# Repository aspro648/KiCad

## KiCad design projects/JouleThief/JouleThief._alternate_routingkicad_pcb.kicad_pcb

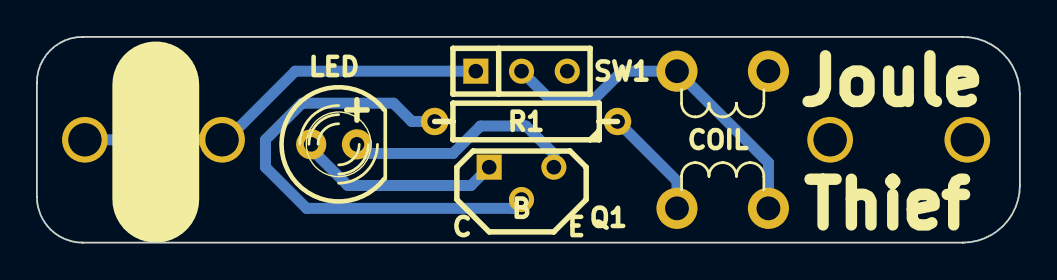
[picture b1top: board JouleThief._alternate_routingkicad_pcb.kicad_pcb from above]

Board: 2 copper layers, 54.6 x 11.4 mm, 6 parts (0 on the bottom side), 6 nets.

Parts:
BT1: BATTERY; BAT_CLIP
LED: LED; LED-5MM
Q1: PN2222A; TO92-123
R1: 1000; R4
SW1: SPST; MICROSWITCH_SPST
T1: COIL; TRANS_JOULE_THIEF

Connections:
/GND: BT1.2, LED.2, Q1.1
unnamed: LED.1, Q1.3, T1.3
unnamed: Q1.2, R1.2
unnamed: R1.1, T1.2
unnamed: SW1.2, T1.1, T1.4
unnamed: BT1.1, SW1.1

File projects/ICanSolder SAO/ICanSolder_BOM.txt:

1 ea., SW1 SWITCH SLIDE SPDT, E-Switch EG1218, https://www.digikey.com/product-detail/en/EG1218/EG1903-ND/101726
1 ea., D1 330 Ohm 1/8w resistor, Stackpole CF18JT330R, http://www.digikey.com/short/7zzrbn
1 ea., R1 5mm Red LED, SunLED XLUR12D, http://www.digikey.com/short/7hrv5j
1 ea., BT1 CR2032 Batt retainer, Linx BAT-HLD-001-THM, https://www.digikey.com/product-detail/en/BAT-HLD-001-THM/BA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
1 ea., CR2032 Battery

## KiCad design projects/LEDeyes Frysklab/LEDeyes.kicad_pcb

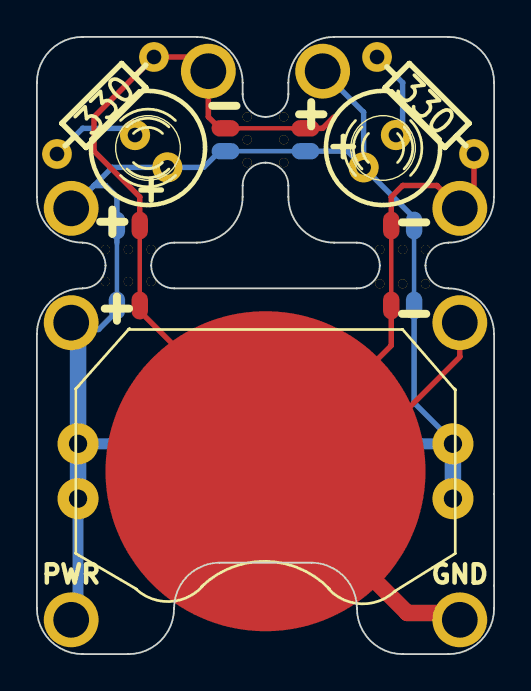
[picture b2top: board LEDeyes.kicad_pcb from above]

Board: 2 copper layers, 25.4 x 34.3 mm, 19 parts (0 on the bottom side), 4 nets.

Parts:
BT1: BATTERY; BATT_CR2032
B_N1, B_N2: GND; 1pin-Sew-thin
B_P1, B_P2: PWR; 1pin-Sew-thin
D1, D2: LED; LED-5MM
L1, L1_C1, L1_C2, L2: 1pin-Sew-thin
R1, R2: 330; R3-LARGE_PADS
p: P; 3hole_mousebite
p#2, p#3, p#4, p#5, p#6: P; 3hole_mousebite

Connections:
GND: BT1.2, B_N1.1, B_N2.1, L1_C1.1, L2.1, R1.1, R2.1
unnamed: BT1.1, B_P1.1, B_P2.1, D1.1, D2.1, L1.1, L1_C2.1
unnamed: D2.2, R2.2
unnamed: D1.2, R1.2
